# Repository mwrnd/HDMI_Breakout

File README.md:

**Work-In-Progress**: [Gerbers produced](https://github.com/mwrnd/HDMI_Breakout/releases/tag/v0.1-alpha) and awaiting testing.

# HDMI Breakout

[HDMI](https://en.wikipedia.org/wiki/HDMI) to [U.FL/UMCC Connector](https://en.wikipedia.org/wiki/Hirose_U.FL) breakout.

[hdmi_pmod](https://github.com/adwranovsky/hdmi_pmod) is a similar project but with a [PMOD](https://en.wikipedia.org/wiki/Pmod_Interface) interface.

# PCB Layout

All differential signals are length-matched to within 1mm, both inter-pair and intra-pair.

I used the KiCad-included symbol and footprint for the [10029449-111RLF](https://www.digikey.com/en/products/detail/amphenol-cs-fci/10029449-111RLF/2785386). The U.FL/UMCC connectors can be [CONUFL001-SMD-T](https://www.trustedparts.com/en/search/CONUFL001-SMD-T) or [U.FL-R-SMT](https://www.trustedparts.com/en/search/U.FL-R-SMT).

# Schematic

# PCB Layer Stackup

4-Layer PCB stackup taken from [JLCPCB](https://jlcpcb.com/capabilities/pcb-capabilities).

100-ohm Differential Impedance parameters were calculated using the [DigiKey Online Calculator](https://www.digikey.com/en/resources/conversion-calculators/conversion-calculator-pcb-trace-impedance).

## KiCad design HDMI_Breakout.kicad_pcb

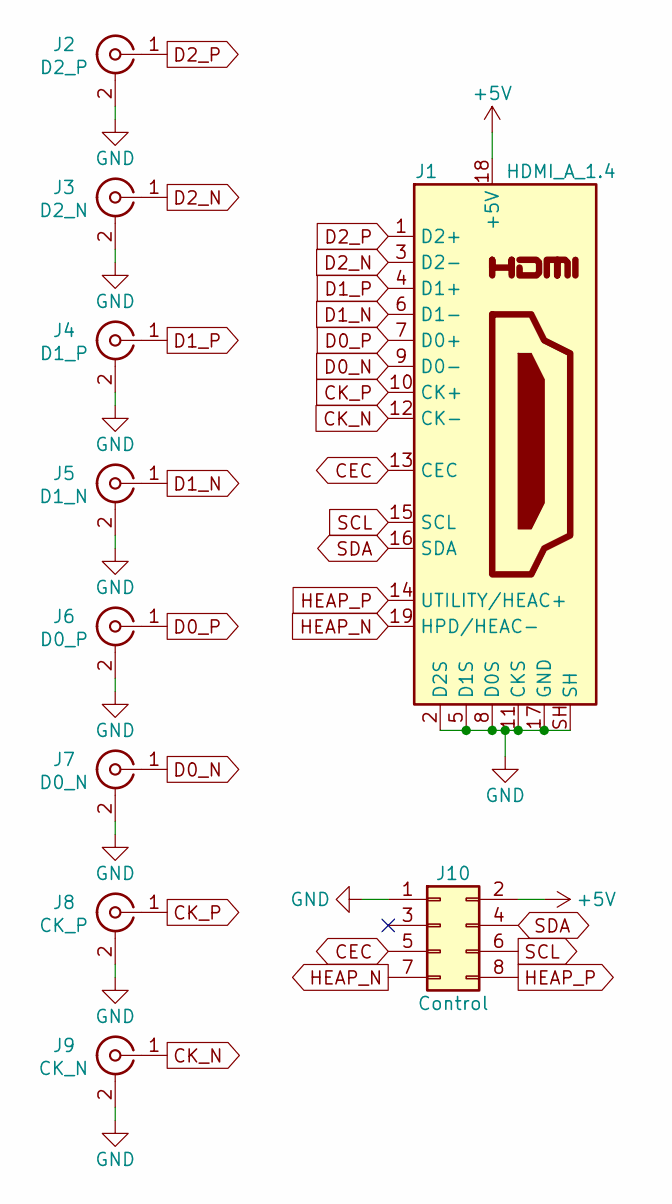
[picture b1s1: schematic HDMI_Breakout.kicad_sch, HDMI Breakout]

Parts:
J1: HDMI_A_1.4; HDMI_A_Amphenol_10029449-x01xLF_Horizontal
J2: D2_P; U.FL_Hirose_w_Label
J3: D2_N; U.FL_Hirose_w_Label
J4: D1_P; U.FL_Hirose_w_Label
J5: D1_N; U.FL_Hirose_w_Label
J6: D0_P; U.FL_Hirose_w_Label
J7: D0_N; U.FL_Hirose_w_Label
J8: CK_P; U.FL_Hirose_w_Label
J9: CK_N; U.FL_Hirose_w_Label
J10: Control; PinSocket_2x04_P2.54mm_Vertical

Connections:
+5V: J1.18 (+5V), J10.2
CEC: J1.13 (CEC), J10.5
CK_N: J1.12 (CK-), J9.1 (In)
CK_P: J1.10 (CK+), J8.1 (In)
D0_N: J1.9 (D0-), J7.1 (In)
D0_P: J1.7 (D0+), J6.1 (In)
D1_N: J1.6 (D1-), J5.1 (In)
D1_P: J1.4 (D1+), J4.1 (In)
D2_N: J1.3 (D2-), J3.1 (In)
D2_P: J1.1 (D2+), J2.1 (In)
GND: J1.2 (D2S), J1.5 (D1S), J1.8 (D0S), J1.11 (CKS), J1.17 (GND), J1.SH, J2.2 (Ext), J3.2 (Ext), J4.2 (Ext), J5.2 (Ext), J6.2 (Ext), J7.2 (Ext), J8.2 (Ext), J9.2 (Ext), J10.1
HEAP_N: J1.19 (HPD/HEAC-), J10.7
HEAP_P: J1.14 (UTILITY/HEAC+), J10.8
SCL: J1.15 (SCL), J10.6
SDA: J1.16 (SDA), J10.4

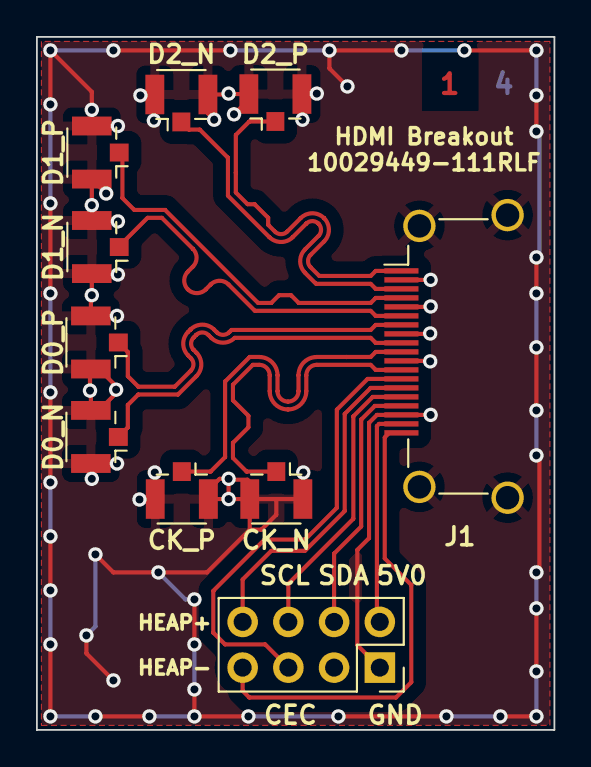
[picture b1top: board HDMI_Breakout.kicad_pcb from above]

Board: 4 copper layers, 28.8 x 38.5 mm, 10 parts (0 on the bottom side), 15 nets.

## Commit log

2023-06-12 First Revision
